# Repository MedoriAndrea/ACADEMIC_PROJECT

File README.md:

# Academic Projects – Andrea Medori

Collection of university projects developed during my studies in Biomedical Engineering at **Università Campus Bio-Medico di Roma**.
Many projects were carried out as group work with fellow students; each folder contains its own README with details.

## Projects

| Project | Course | Topics | Period |
|---|---|---|---|
| [Retinal Disease Analysis on ODIR](Digital_Signal_and_Image_Processing/) | Digital Signal and Image Processing | Image processing, feature extraction (colour, GLCM), statistical tests, CNN, nested cross-validation | Jan–Feb 2025 |
| [Teleoperated Mobile Robot – Odometry & EKF](Mechatronics_Mobile_Robot/) | Mechatronics (group) | Embedded C (PIC), I²C encoders, Bluetooth, MATLAB GUI, odometry, Extended Kalman Filter | Nov 2024–Jun 2025 |
| [4-DOF LEGO EV3 Manipulator – Kinematics & Redundancy](Robotics_EV3_Manipulator/) | Industrial and Medical Robotics | DH, forward/inverse kinematics (CLIK), trajectory planning, redundancy resolution, dynamic model, LEGO EV3 (Python) | Mar–Jun 2025 |
| [Real-Time Dance Step Recognition from Smartphone IMU](Automation_HAR_Dance_Steps_Simulink/) | Automation and Workplace Safety (group) | Simulink + Android sensors, band-pass filtering, event windowing, 162 features, PCA, SVM / boosted trees, real-time classification | Dec 2025–Feb 2026 |
| [AddiKid Hand – Pediatric Prosthetic Hand](Biodesign_Pediatric_Prosthetic_Hand/) | Biodesign (group) | Underactuated tendon transmission, actuator sizing, fingertip force model, sEMG/FMG/IMU sensing, custom PCB (ATmega328P, BLE), CAD | Sep 2025–Jan 2026 |
| [Human Hand vs Robolimb – Kinematic Analysis](Biomechanics_Human_vs_Robolimb_Kinematics/) | Bioengineering and Biomechanics of Human Movement (group) | Marker-based video tracking, Kalman filter, PyQt6 GUI, UDP robot control, YOLO, kinematic features, non-parametric statistics | May–Jun 2026 |
| [PillBro – IoMT Smart Pill Dispenser](IoMT_PillBro_Smart_Pill_Dispenser/) | Internet of Medical Things (group) | 3-tier IoMT architecture, MQTT, UART, Cisco Packet Tracer simulation, LLM voice companion (design), business model | May–Jun 2026 |
| [ICD-10 Chapter Prediction](Machine_Learning_ICD10_Chapter_Prediction/) | Machine Learning and Big Data Analytics (group) | Clinical tabular data, feature engineering, statistical feature selection, LR/SVM/RF/XGBoost, nested CV, ablation study | May–Jul 2026 |
| [Hand of Hope – Clinical Investigation Protocol](Rehabilitation_HandOfHope_Clinical_Protocol/) | Rehabilitation Bioengineering (group, with physiotherapists) | EMG-driven hand exoskeleton, post-stroke rehabilitation, MDR clinical protocol, endpoints (FMA-UE, ARAT…), statistical analysis plan | Jan 2026 |

*More projects will be added.*

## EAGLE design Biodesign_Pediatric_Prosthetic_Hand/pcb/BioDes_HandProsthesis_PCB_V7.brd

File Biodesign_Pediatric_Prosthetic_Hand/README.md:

# AddiKid Hand: Bio-Inspired Underactuated Pediatric Prosthetic Hand

Group project (**Group E**, 11 students) for the **Biodesign** course, MSc in Biomedical Engineering, Università Campus Bio-Medico di Roma, A.Y. 2025/2026 (Sep 2025 – Jan 2026).

The goal was to design a **low-cost, bio-inspired prosthetic hand for a 12-year-old child**, combining additive manufacturing, flexure hinges, an underactuated tendon transmission, and hybrid sensing for myoelectric control.

---

## Requirements
- **Functional:** the main daily grasps (lateral, cylindrical, spherical); smooth and coordinated finger motion; intuitive control with low cognitive load.
- **Pediatric safety:** intrinsic passive safety, limited force and speed, low weight, quiet operation, biocompatible materials.
- **Mechanical:** pediatric anatomy (palm sized from anthropometric data for children aged 5–13), modular parts that can follow the child's growth, robustness to impacts.
- **System:** daily-use battery life, compatibility with EMG control, fail-safe behaviour, **cost under €1,000**.

## Mechanical design and actuation
- **Actuation options compared:** dielectric elastomer actuators (DEA), vacuum-driven pneumatic actuators (VAMP, with micro pump and microvalve), and **electric actuation**.
- **Selected actuator:** FAULHABER 1627 GXR DC micromotor with a 16GPT planetary gearhead (116:1), sized for 100 N maximum tendon tension, 25 mm stroke and a 2 s closing time, which requires about 300 mNm of output torque.
- **Underactuated differential transmission:** a single motor drives all five fingers through a cascade of mobile pulleys. Each finger stops on its own when it touches the object, and the force is passively redistributed: 100 N → 50/50 N → 25 N for thumb, index and middle, 12.5 N for ring and little finger.
- **Thumb:** a cam-based passive locking mechanism with 3 stable positions: 20° for lateral grasp, 50° for cylindrical grasp, 90° for full opposition.
- **Fingertip force:** each finger is modelled as a planar 2-DoF manipulator, and the fingertip force comes from τ = Jᵀ F (virtual work). With 25 N of tendon tension in a pinch grip: **thumb ≈ 11.3 N, index ≈ 8.7 N**, consistent with values reported in the literature.

## Electronic design
- **Hybrid sensing for pattern-recognition control (regression-based, simultaneous and proportional):**
  - **sEMG** (OYMotion analog EMG sensor) captures early muscle activation;
  - **FMG** (Interlink FSR400 force sensors) is robust to environmental and physiological factors;
  - **IMU** (Bosch BNO055) compensates for arm position and enables a smart standby mode.
- **Custom PCB (Eagle/Fusion), V7**, organised in 3 areas:
  - **Logic and control:** ATmega328P, ICSP programming port, reset button, sleep button.
  - **Sensing and communication:** sensor inputs (with voltage dividers for the FSRs), IMU interrupt line, nRF51822 Bluetooth Low Energy chip with meander antenna, Bluetooth on/off button.
  - **Power and actuation:** 3.7 V 4000 mAh LiPo battery, Schottky diode against reverse current, LM1117 5 V regulator, TPS22918 load switch, INA219 voltage/current monitor with battery LED, DRV8837 motor driver.
- **Firmware (designed at block level):** synchronised acquisition of sEMG, FMG and IMU; conversion of the signals into proportional, low-latency motor commands; Bluetooth link to a smartphone app for recalibration and saving user profiles.

## Results
| Metric | Value |
|---|---|
| Estimated battery life | ~10 h |
| Total weight | 254.6 g |
| Total cost (bill of materials) | €585.90 (< €1,000 target) |
| Grasps | Lateral, cylindrical, spherical |

**Future work:** a rotating wrist module, more grasp types through adaptive control, use of the IMU to detect impacts, a soft outer covering, and a Bluetooth app for rehabilitation exercises (also in VR/AR).

---

## Repository structure
```
├── cad/hand_group_E.stl         # 3D model of the hand (STL)
├── pcb/
│   ├── BioDes_HandProsthesis_PCB_V7.sch   # Schematic (Eagle)
│   ├── BioDes_HandProsthesis_PCB_V7.brd   # PCB layout (Eagle)
│   └── BioDes_HandProsthesis_PCB_V7.f3d   # Fusion 360 design
└── docs/final_presentation.pdf  # Final presentation (with references)
```

The component datasheets (FAULHABER motor and gearhead, BNO055, FSR, INA219, nRF51822, DRV883x, TPS22918, NeoPixel, LiPo LP105068, Memetis microvalve, vacuum pump) are not included because they belong to their manufacturers. They are available on the manufacturers' websites.

---

*Group project developed with fellow students at Università Campus Bio-Medico di Roma.*

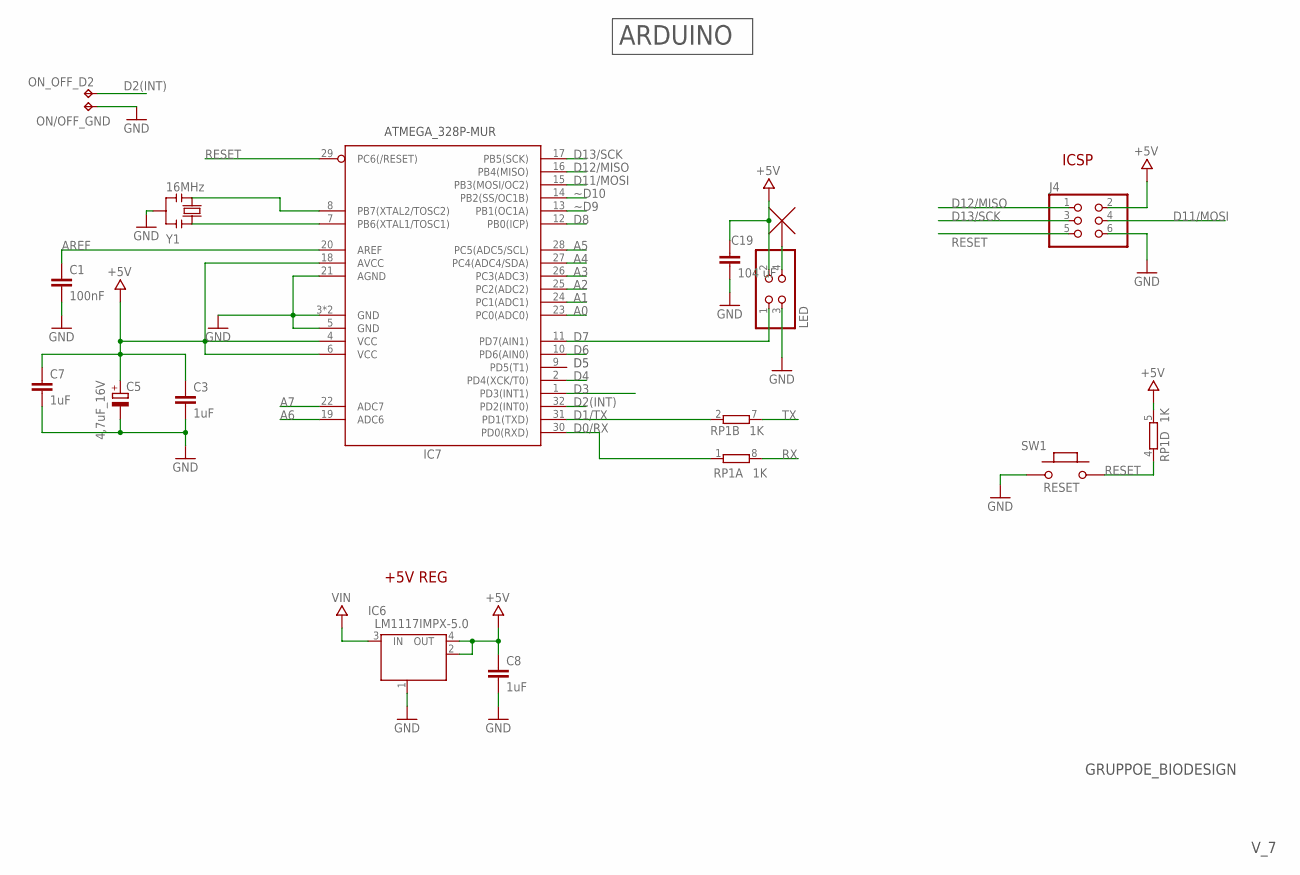
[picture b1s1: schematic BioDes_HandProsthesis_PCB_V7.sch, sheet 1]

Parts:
C1: 100nF; C0603-ROUND; MPN C0603C104K3RACTU
C3, C7, C8: 1uF; C0603-ROUND; MPN C1210F105K5RACTU
C5: 4,7uF_16V; TAN-A; MPN T491A475K016AT
C19: 104 uF; C0603
IC6: LM1117IMPX-5.0; LINEAR_SOT223; MPN NCP1117ST50T3G
IC7: 328P-MUR; VQFN32
J4: 0114_PH254-203DF118A00V; 2X03; MPN 350732-4
LED: PINHD-2X2; 2X02
ON/OFF_GND: TPB1,27; B1,27
ON_OFF_D2: TPB1,27; B1,27
RP1: 1K; CAY16; MPN CRCW04021K00FKED
SW1: RESET; SMD_157SW; MPN MAX1232CPA+
Y1: 16MHz; RESONATOR; MPN ATMEGA16U2-AU

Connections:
+5V: C3.1, C5.1 (+), C7.1, C8.1, C19.1, IC6.2 (OUT), IC6.4 (OUT), IC7.4 (VCC), IC7.6 (VCC), IC7.18 (AVCC), J4.2, LED.2, RP1.5 (2); also elsewhere on the board
A0: IC7.23 (PC0(ADC0)); also elsewhere on the board
A1: IC7.24 (PC1(ADC1)); also elsewhere on the board
A2: IC7.25 (PC2(ADC2)); also elsewhere on the board
A3: IC7.26 (PC3(ADC3)); also elsewhere on the board
A4: IC7.27 (PC4(ADC4/SDA)); also elsewhere on the board
A5: IC7.28 (PC5(ADC5/SCL)); also elsewhere on the board
A6: IC7.19 (ADC6); also elsewhere on the board
A7: IC7.22 (ADC7); also elsewhere on the board
AREF: C1.1, IC7.20 (AREF)
D0/RX: IC7.30 (PD0(RXD)), RP1.1
D1/TX: IC7.31 (PD1(TXD)), RP1.2 (1)
D2(INT): IC7.32 (PD2(INT0)), ON_OFF_D2.TP
D3: IC7.1 (PD3(INT1)); also elsewhere on the board
D4: IC7.2 (PD4(XCK/T0)); also elsewhere on the board
D6: IC7.10 (PD6(AIN0)); also elsewhere on the board
D7: IC7.11 (PD7(AIN1)), LED.1
D8: IC7.12 (PB0(ICP)); also elsewhere on the board
D11/MOSI: IC7.15 (PB3(MOSI/OC2)), J4.4
D12/MISO: IC7.16 (PB4(MISO)), J4.1
D13/SCK: IC7.17 (PB5(SCK)), J4.3
GND: C1.2, C3.2, C5.2 (-), C7.2, C8.2, C19.2, IC6.1 (GND/ADJ), IC7.3 (GND), IC7.5 (GND), IC7.21 (AGND), IC7.33 (GND), J4.6, LED.3, ON/OFF_GND.TP, SW1.1, Y1.2; also elsewhere on the board
unnamed: IC7.7 (PB6(XTAL1/TOSC1)), Y1.1
unnamed: IC7.8 (PB7(XTAL2/TOSC2)), Y1.3
RESET: IC7.29 (PC6(/RESET)), J4.5, RP1.4 (1), SW1.2
RX: RP1.8 (2); also elsewhere on the board
TX: RP1.7 (2); also elsewhere on the board
VIN: IC6.3 (IN); also elsewhere on the board
~D9: IC7.13 (PB1(OC1A)); also elsewhere on the board
~D10: IC7.14 (PB2(SS/OC1B)); also elsewhere on the board

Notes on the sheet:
GRUPPOE_BIODESIGN
V_7
+5V REG
ICSP
ATMEGA_328P-MUR
ARDUINO

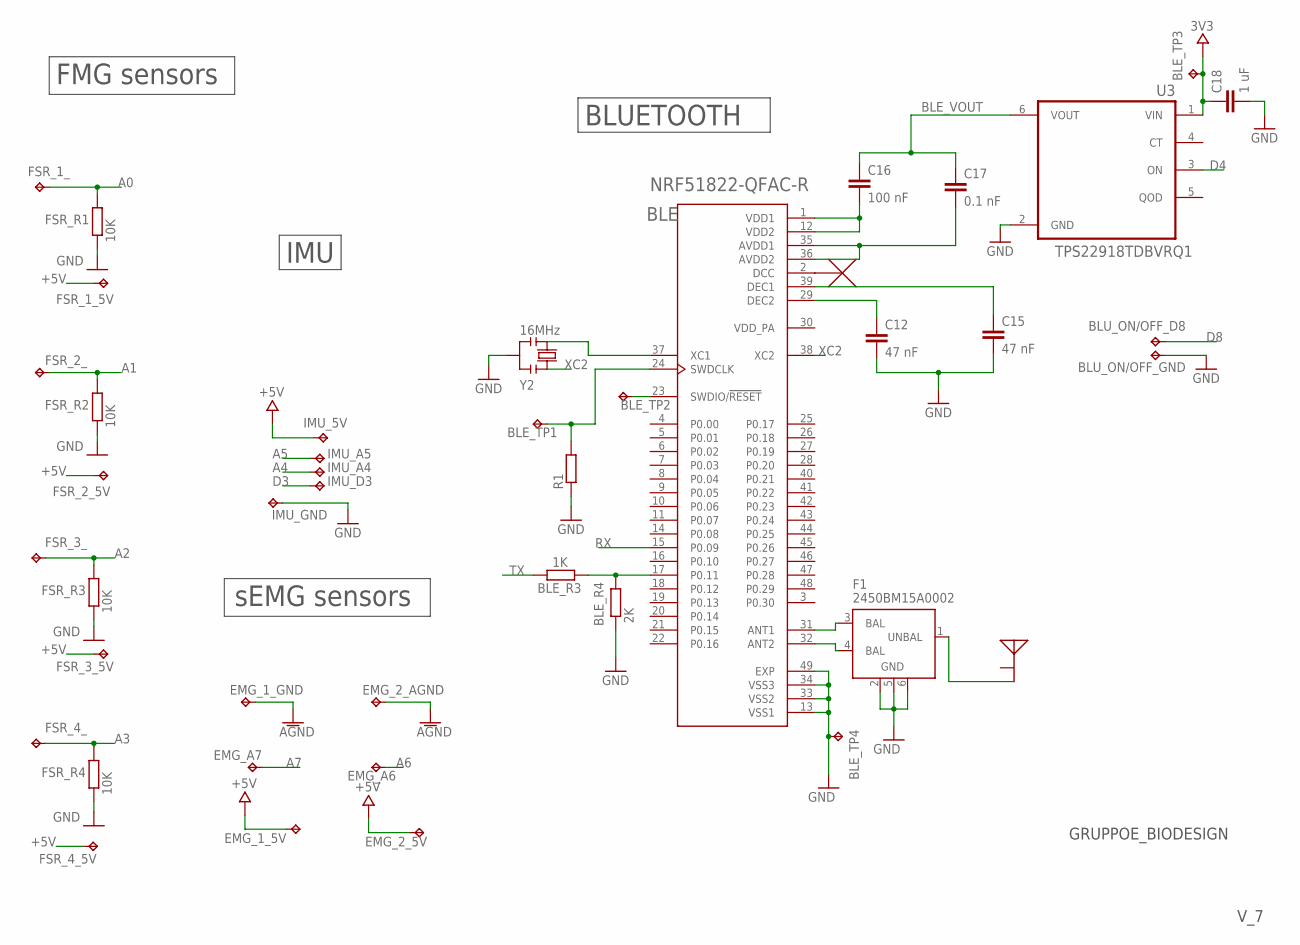
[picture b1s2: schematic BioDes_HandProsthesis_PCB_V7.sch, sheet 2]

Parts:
BLE: NRF51822-QFAC-R; QFN40P600X600X90-49N; MPN NRF51822-QFAC-R7
BLE_R3: 1K; R0603; MPN CRCW04021K00FKED
BLE_R4: 2K; R0603; MPN 47L16-I/P
BLE_TP1, BLE_TP2, BLE_TP3, BLE_TP4: TPB1,27; B1,27
BLU_ON/OFF_D8: TPB1,27; B1,27
BLU_ON/OFF_GND: TPB1,27; B1,27
C12, C15: 47 nF; C0603; MPN MKT1813347405
C16: 100 nF; C0603; MPN C0603C104K3RACTU
C17: 0.1 nF; C0603; MPN CC0402JRNPO9BN101
C18: 1 uF; C0603; MPN C1210F105K5RACTU
EMG_1_5V, EMG_1_GND, EMG_2_5V, EMG_2_AGND: TPB1,27; B1,27
EMG_A6, EMG_A7: TPB1,27; B1,27
F1: 2450BM15A0002; MPN 2450BM15A0002E
FSR_1_, FSR_1_5V, FSR_2_, FSR_2_5V, FSR_3_, FSR_3_5V, FSR_4_, FSR_4_5V: TPB1,27; B1,27
FSR_R1, FSR_R2, FSR_R3, FSR_R4: 10K; R0603; MPN CRCW080510K0FKEA
IMU_5V: TPB1,27; B1,27
IMU_A4, IMU_A5: TPB1,27; B1,27
IMU_D3: TPB1,27; B1,27
IMU_GND: TPB1,27; B1,27
R1: R-EU_R0603; R0603; MPN SS21V-R060330
U3: TPS22918TDBVRQ1; SOT95P280X145-6N; MPN TPS22945DCKR
U$11: MEANDER-ANT
Y2: 16MHz; RESONATOR; MPN ATMEGA16U2-AU

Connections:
3V3: BLE_TP3.TP, C18.1, U3.1 (VIN)
+5V: EMG_1_5V.TP, EMG_2_5V.TP, FSR_1_5V.TP, FSR_2_5V.TP, FSR_3_5V.TP, FSR_4_5V.TP, IMU_5V.TP; also elsewhere on the board
A0: FSR_1_.TP, FSR_R1.2; also elsewhere on the board
A1: FSR_2_.TP, FSR_R2.2; also elsewhere on the board
A2: FSR_3_.TP, FSR_R3.2; also elsewhere on the board
A3: FSR_4_.TP, FSR_R4.2; also elsewhere on the board
A4: IMU_A4.TP; also elsewhere on the board
A5: IMU_A5.TP; also elsewhere on the board
A6: EMG_A6.TP; also elsewhere on the board
A7: EMG_A7.TP; also elsewhere on the board
BLE_VOUT: C16.1, C17.1, U3.6 (VOUT)
D3: IMU_D3.TP; also elsewhere on the board
D4: U3.3 (ON); also elsewhere on the board
D8: BLU_ON/OFF_D8.TP; also elsewhere on the board
GND: BLE.13 (VSS1), BLE.33 (VSS2), BLE.34 (VSS3), BLE.49 (EXP), BLE_R4.1, BLE_TP4.TP, BLU_ON/OFF_GND.TP, C12.2, C15.2, C18.2, EMG_1_GND.TP, EMG_2_AGND.TP, F1.2 (GND), F1.5 (GND), F1.6 (GND), FSR_R1.1, FSR_R2.1, FSR_R3.1, FSR_R4.1, IMU_GND.TP, R1.1, U3.2 (GND), Y2.2; also elsewhere on the board
unnamed: BLE.24 (SWDCLK), BLE_TP1.TP, R1.2
unnamed: BLE.23 (SWDIO/!RESET), BLE_TP2.TP
unnamed: F1.1 (UNBAL), U$11.FEED
unnamed: BLE.31 (ANT1), F1.3 (BAL)
unnamed: BLE.32 (ANT2), F1.4 (BAL)
unnamed: BLE.29 (DEC2), C12.1
unnamed: BLE.17 (P0.11), BLE_R3.1, BLE_R4.2
unnamed: BLE.39 (DEC1), C15.1
unnamed: BLE.1 (VDD1), BLE.12 (VDD2), C16.2
unnamed: BLE.35 (AVDD1), BLE.36 (AVDD2), C17.2
unnamed: BLE.37 (XC1), Y2.3
RX: BLE.15 (P0.09); also elsewhere on the board
TX: BLE_R3.2; also elsewhere on the board
XC2: BLE.38 (XC2), Y2.1

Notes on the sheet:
FMG sensors
IMU
sEMG sensors
BLUETOOTH
GRUPPOE_BIODESIGN
V_7

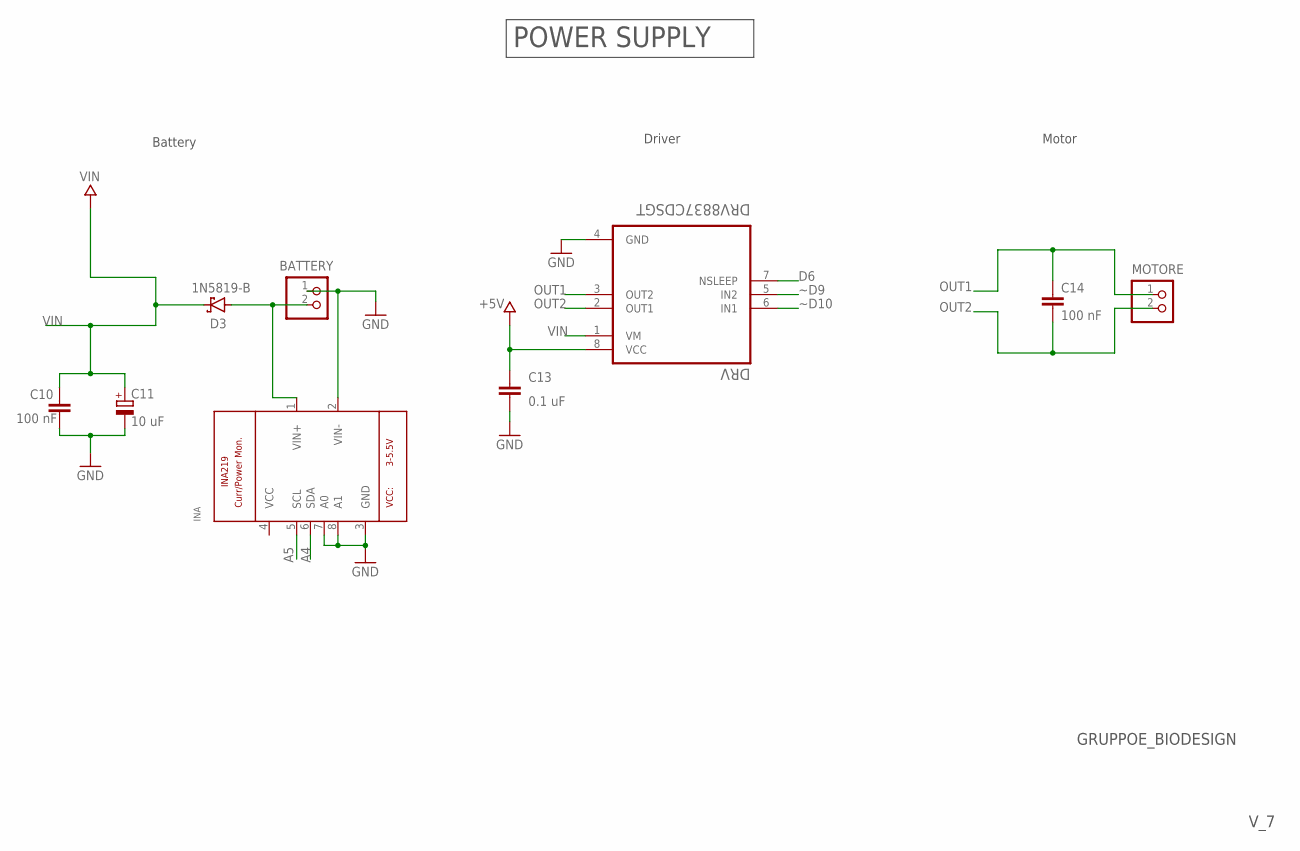
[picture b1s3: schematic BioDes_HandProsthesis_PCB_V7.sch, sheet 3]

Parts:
BATTERY: PINHD-1X2/90; 1X02/90
C10, C14: 100 nF; C0603; MPN C0603C104K3RACTU
C11: 10 uF; A/3216-18R; MPN CGA5L1X7R1E106K160AC
C13: 0.1 uF; C0603; MPN C0603C104K3RACTU
D3: 1N5819-B; DO41-7.6; MPN 1N5819-E3/54
DRV: DRV8837CDSGT; SON50P200X200X80-9N; MPN DRV8832DGQR
INA: INA219; SOT23-8; MPN MAX6369KA+T
MOTORE: PINHD-1X2/90; 1X02/90

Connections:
+5V: C13.1, DRV.8 (VCC); also elsewhere on the board
A4: INA.6 (SDA); also elsewhere on the board
A5: INA.5 (SCL); also elsewhere on the board
D6: DRV.7 (NSLEEP); also elsewhere on the board
GND: BATTERY.1, C10.2, C11.-, C13.2, DRV.4 (GND), INA.2 (VIN-), INA.3 (GND), INA.7 (A0), INA.8 (A1); also elsewhere on the board
unnamed: BATTERY.2, D3.A, INA.1 (VIN+)
OUT1: C14.1, DRV.3 (OUT2), MOTORE.1
OUT2: C14.2, DRV.2 (OUT1), MOTORE.2
VIN: C10.1, C11.+, D3.C, DRV.1 (VM); also elsewhere on the board
~D9: DRV.5 (IN2); also elsewhere on the board
~D10: DRV.6 (IN1); also elsewhere on the board

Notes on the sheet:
POWER SUPPLY
Battery
Driver
Motor
GRUPPOE_BIODESIGN
V_7

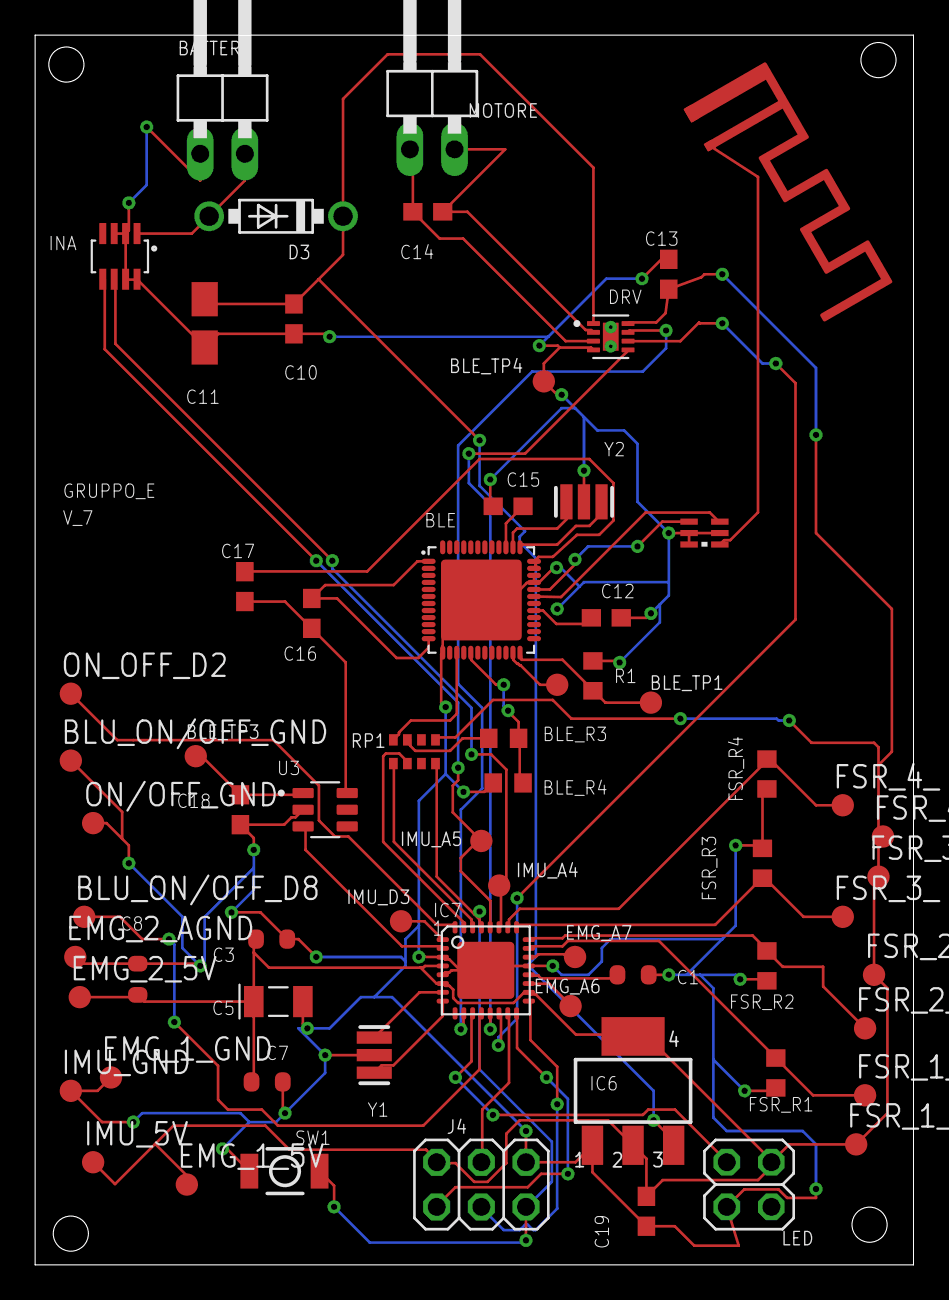
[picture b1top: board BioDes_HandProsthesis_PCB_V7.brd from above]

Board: 2 copper layers, 50.0 x 70.0 mm, 66 parts (0 on the bottom side), 47 nets.

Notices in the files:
parts and their libraries:
Arduino-ucs: Copyright (c) 2016-2017 Arduino LLC.  All right reserved.
